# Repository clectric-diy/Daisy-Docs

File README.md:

# DaisyDocs
An augmented collection of the documentation provided by daisy.audio.

Documents in the [source folder](source) are those provided by daisy.audio under the MIT License.

clectric.diy community documents should be added to the [community folder](community).

All of the documentation in this repository is shared under the CC BY-SA license.

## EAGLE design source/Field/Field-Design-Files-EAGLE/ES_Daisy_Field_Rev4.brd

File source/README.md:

daisy.audio Documentation

All documentation in this source folder has been provided by daisy.audio under the MIT License.

Please see the [community folder](../community) for documentation created by the clectric.diy Community to augment what has been provided by daisy.audio.

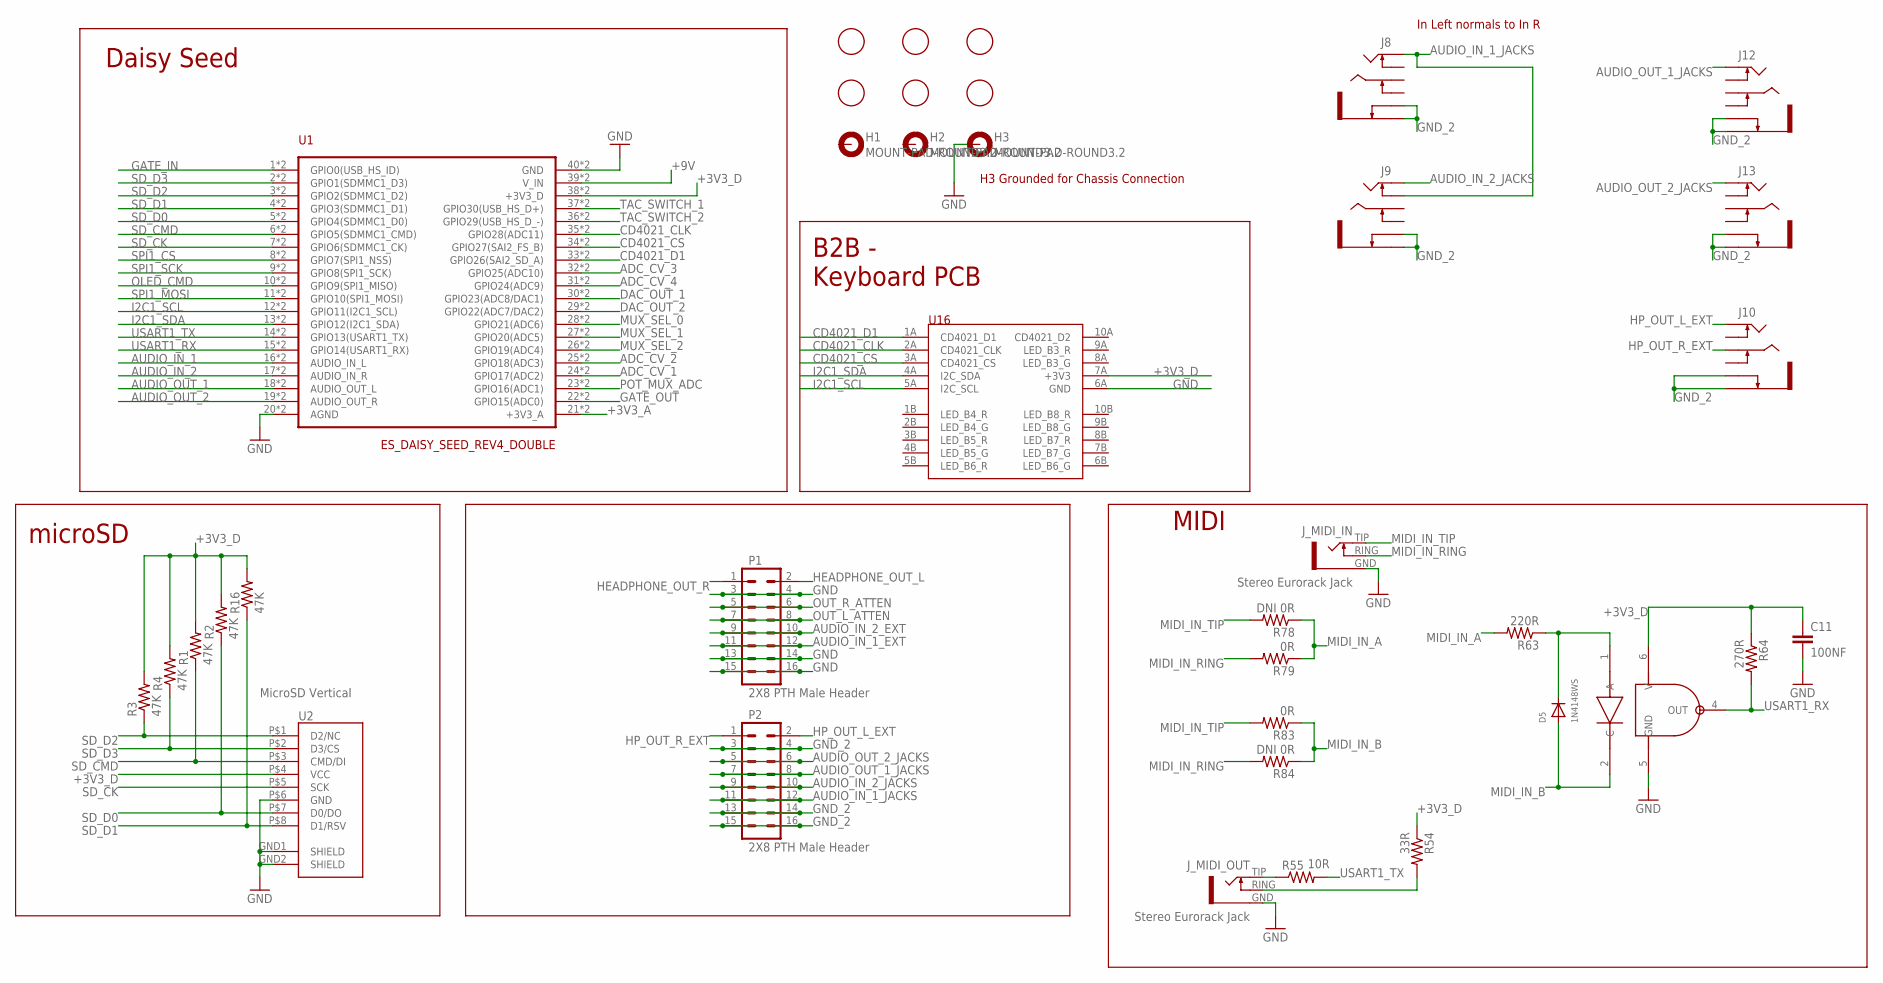
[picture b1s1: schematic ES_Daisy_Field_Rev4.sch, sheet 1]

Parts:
C11: 100NF; C0603
D5: 1N4148WS; SOD-323F
FD1, FD2, FD3, FD4, FD5, FD6: FIDUCIAL; FIDUCIAL_1MM
H1, H2, H3: MOUNT-PAD-ROUND3.2; 32-PAD
J8, J9, J10, J12, J13: PTH Switching Stereo Guitar Jack; WQP-PJ6110
J_MIDI_IN: Stereo Eurorack Jack; STEREO_JACK_3.5MM
J_MIDI_OUT: Stereo Eurorack Jack; STEREO_JACK_3.5MM
P1, P2: 2X8 PTH Male Header; 2X8_LOCK
R1, R2, R3, R4, R16: 47K; R0603
R54: 33R; R0603
R55: 10R; R0603
R63: 220R; R0603
R64: 270R; R0603
R78, R84: DNI 0R; R0603
R79, R83: 0R; R0603
U1: ES_DAISY_SEED_REV4_DOUBLE; ES_DAISY_SEED_DOUBLE
U2: MicroSD Vertical; VERT_MICROSD_CENTERED
U15: OPTO ISOLATOR; DIL06_GULLWING
U16: ES_KEYBOARD_SM_REV2_ALIGNED

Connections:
+3V3_A: U1.21 (+3V3_A), U1.B21 (+3V3_A); also elsewhere on the board
+3V3_D: C11.1, R1.2, R2.2, R3.2, R4.2, R16.2, R54.1, R64.1, U1.38 (+3V3_D), U1.B38 (+3V3_D), U2.P$4 (VCC), U15.6 (V), U16.7A (+3V3); also elsewhere on the board
+9V: U1.39 (V_IN), U1.B39 (V_IN); also elsewhere on the board
ADC_CV_1: U1.24 (GPIO17(ADC2)), U1.B24 (GPIO17(ADC2)); also elsewhere on the board
ADC_CV_2: U1.25 (GPIO18(ADC3)), U1.B25 (GPIO18(ADC3)); also elsewhere on the board
ADC_CV_3: U1.32 (GPIO25(ADC10)), U1.B32 (GPIO25(ADC10)); also elsewhere on the board
ADC_CV_4: U1.31 (GPIO24(ADC9)), U1.B31 (GPIO24(ADC9)); also elsewhere on the board
AUDIO_IN_1: U1.16 (AUDIO_IN_L), U1.B16 (AUDIO_IN_L); also elsewhere on the board
AUDIO_IN_1_EXT: P1.11, P1.12; also elsewhere on the board
AUDIO_IN_1_JACKS: J8.2 (TIP), J9.5 (TIP_SW), P2.11, P2.12
AUDIO_IN_2: U1.17 (AUDIO_IN_R), U1.B17 (AUDIO_IN_R); also elsewhere on the board
AUDIO_IN_2_EXT: P1.9, P1.10; also elsewhere on the board
AUDIO_IN_2_JACKS: J9.2 (TIP), P2.9, P2.10
AUDIO_OUT_1: U1.18 (AUDIO_OUT_L), U1.B18 (AUDIO_OUT_L); also elsewhere on the board
AUDIO_OUT_1_JACKS: J12.2 (TIP), P2.7, P2.8
AUDIO_OUT_2: U1.19 (AUDIO_OUT_R), U1.B19 (AUDIO_OUT_R); also elsewhere on the board
AUDIO_OUT_2_JACKS: J13.2 (TIP), P2.5, P2.6
CD4021_CLK: U1.35 (GPIO28(ADC11)), U1.B35 (GPIO28(ADC11)), U16.2A (CD4021_CLK)
CD4021_CS: U1.34 (GPIO27(SAI2_FS_B)), U1.B34 (GPIO27(SAI2_FS_B)), U16.3A (CD4021_CS)
CD4021_D1: U1.33 (GPIO26(SAI2_SD_A)), U1.B33 (GPIO26(SAI2_SD_A)), U16.1A (CD4021_D1)
DAC_OUT_1: U1.30 (GPIO23(ADC8/DAC1)), U1.B30 (GPIO23(ADC8/DAC1)); also elsewhere on the board
DAC_OUT_2: U1.29 (GPIO22(ADC7/DAC2)), U1.B29 (GPIO22(ADC7/DAC2)); also elsewhere on the board
GATE_IN: U1.1 (GPIO0(USB_HS_ID)), U1.B1 (GPIO0(USB_HS_ID)); also elsewhere on the board
GATE_OUT: U1.22 (GPIO15(ADC0)), U1.B22 (GPIO15(ADC0)); also elsewhere on the board
GND: C11.2, H3.B3,2, J_MIDI_IN.GND, J_MIDI_OUT.GND, P1.3, P1.4, P1.13, P1.14, P1.15, P1.16, U1.20 (AGND), U1.40 (GND), U1.B20 (AGND), U1.B40 (GND), U2.GND1 (SHIELD), U2.GND2 (SHIELD), U2.P$6 (GND), U15.5 (GND), U16.6A (GND); also elsewhere on the board
GND_2: J8.1 (SLEEVE), J8.4 (SLEEVE_SW), J9.1 (SLEEVE), J9.4 (SLEEVE_SW), J10.1 (SLEEVE), J10.4 (SLEEVE_SW), J12.1 (SLEEVE), J12.4 (SLEEVE_SW), J13.1 (SLEEVE), J13.4 (SLEEVE_SW), P2.3, P2.4, P2.13, P2.14, P2.15, P2.16
HEADPHONE_OUT_L: P1.2; also elsewhere on the board
HEADPHONE_OUT_R: P1.1; also elsewhere on the board
HP_OUT_L_EXT: J10.2 (TIP), P2.2
HP_OUT_R_EXT: J10.3 (RING), P2.1
I2C1_SCL: U1.12 (GPIO11(I2C1_SCL)), U1.B12 (GPIO11(I2C1_SCL)), U16.5A (I2C_SCL); also elsewhere on the board
I2C1_SDA: U1.13 (GPIO12(I2C1_SDA)), U1.B13 (GPIO12(I2C1_SDA)), U16.4A (I2C_SDA); also elsewhere on the board
MIDI_IN_A: R63.2, R78.1, R79.1
MIDI_IN_B: D5.A, R83.1, R84.1, U15.2 (C)
MIDI_IN_RING: J_MIDI_IN.RING (NORM), R79.2, R84.2
MIDI_IN_TIP: J_MIDI_IN.TIP, R78.2, R83.2
MUX_SEL_0: U1.28 (GPIO21(ADC6)), U1.B28 (GPIO21(ADC6)); also elsewhere on the board
MUX_SEL_1: U1.27 (GPIO20(ADC5)), U1.B27 (GPIO20(ADC5)); also elsewhere on the board
MUX_SEL_2: U1.26 (GPIO19(ADC4)), U1.B26 (GPIO19(ADC4)); also elsewhere on the board
unnamed: J_MIDI_OUT.TIP, R55.1
unnamed: J_MIDI_OUT.RING (NORM), R54.2
unnamed: D5.C, R63.1, U15.1 (A)
OLED_CMD: U1.10 (GPIO9(SPI1_MISO)), U1.B10 (GPIO9(SPI1_MISO)); also elsewhere on the board
OUT_L_ATTEN: P1.7, P1.8; also elsewhere on the board
OUT_R_ATTEN: P1.5, P1.6; also elsewhere on the board
POT_MUX_ADC: U1.23 (GPIO16(ADC1)), U1.B23 (GPIO16(ADC1)); also elsewhere on the board
SD_CK: U1.7 (GPIO6(SDMMC1_CK)), U1.B7 (GPIO6(SDMMC1_CK)), U2.P$5 (SCK)
SD_CMD: R1.1, U1.6 (GPIO5(SDMMC1_CMD)), U1.B6 (GPIO5(SDMMC1_CMD)), U2.P$3 (CMD/DI)
SD_D0: R2.1, U1.5 (GPIO4(SDMMC1_D0)), U1.B5 (GPIO4(SDMMC1_D0)), U2.P$7 (D0/DO)
SD_D1: R16.1, U1.4 (GPIO3(SDMMC1_D1)), U1.B4 (GPIO3(SDMMC1_D1)), U2.P$8 (D1/RSV)
SD_D2: R3.1, U1.3 (GPIO2(SDMMC1_D2)), U1.B3 (GPIO2(SDMMC1_D2)), U2.P$1 (D2/NC)
SD_D3: R4.1, U1.2 (GPIO1(SDMMC1_D3)), U1.B2 (GPIO1(SDMMC1_D3)), U2.P$2 (D3/CS)
SPI1_CS: U1.8 (GPIO7(SPI1_NSS)), U1.B8 (GPIO7(SPI1_NSS)); also elsewhere on the board
SPI1_MOSI: U1.11 (GPIO10(SPI1_MOSI)), U1.B11 (GPIO10(SPI1_MOSI)); also elsewhere on the board
SPI1_SCK: U1.9 (GPIO8(SPI1_SCK)), U1.B9 (GPIO8(SPI1_SCK)); also elsewhere on the board
TAC_SWITCH_1: U1.37 (GPIO30(USB_HS_D+)), U1.B37 (GPIO30(USB_HS_D+)); also elsewhere on the board
TAC_SWITCH_2: U1.36 (GPIO29(USB_HS_D_-)), U1.B36 (GPIO29(USB_HS_D_-)); also elsewhere on the board
USART1_RX: R64.2, U1.15 (GPIO14(USART1_RX)), U1.B15 (GPIO14(USART1_RX)), U15.4 (OUT)
USART1_TX: R55.2, U1.14 (GPIO13(USART1_TX)), U1.B14 (GPIO13(USART1_TX))

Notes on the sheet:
Daisy Seed
microSD
B2B - Keyboard PCB
MIDI
H3 Grounded for Chassis Connection
In Left normals to In R

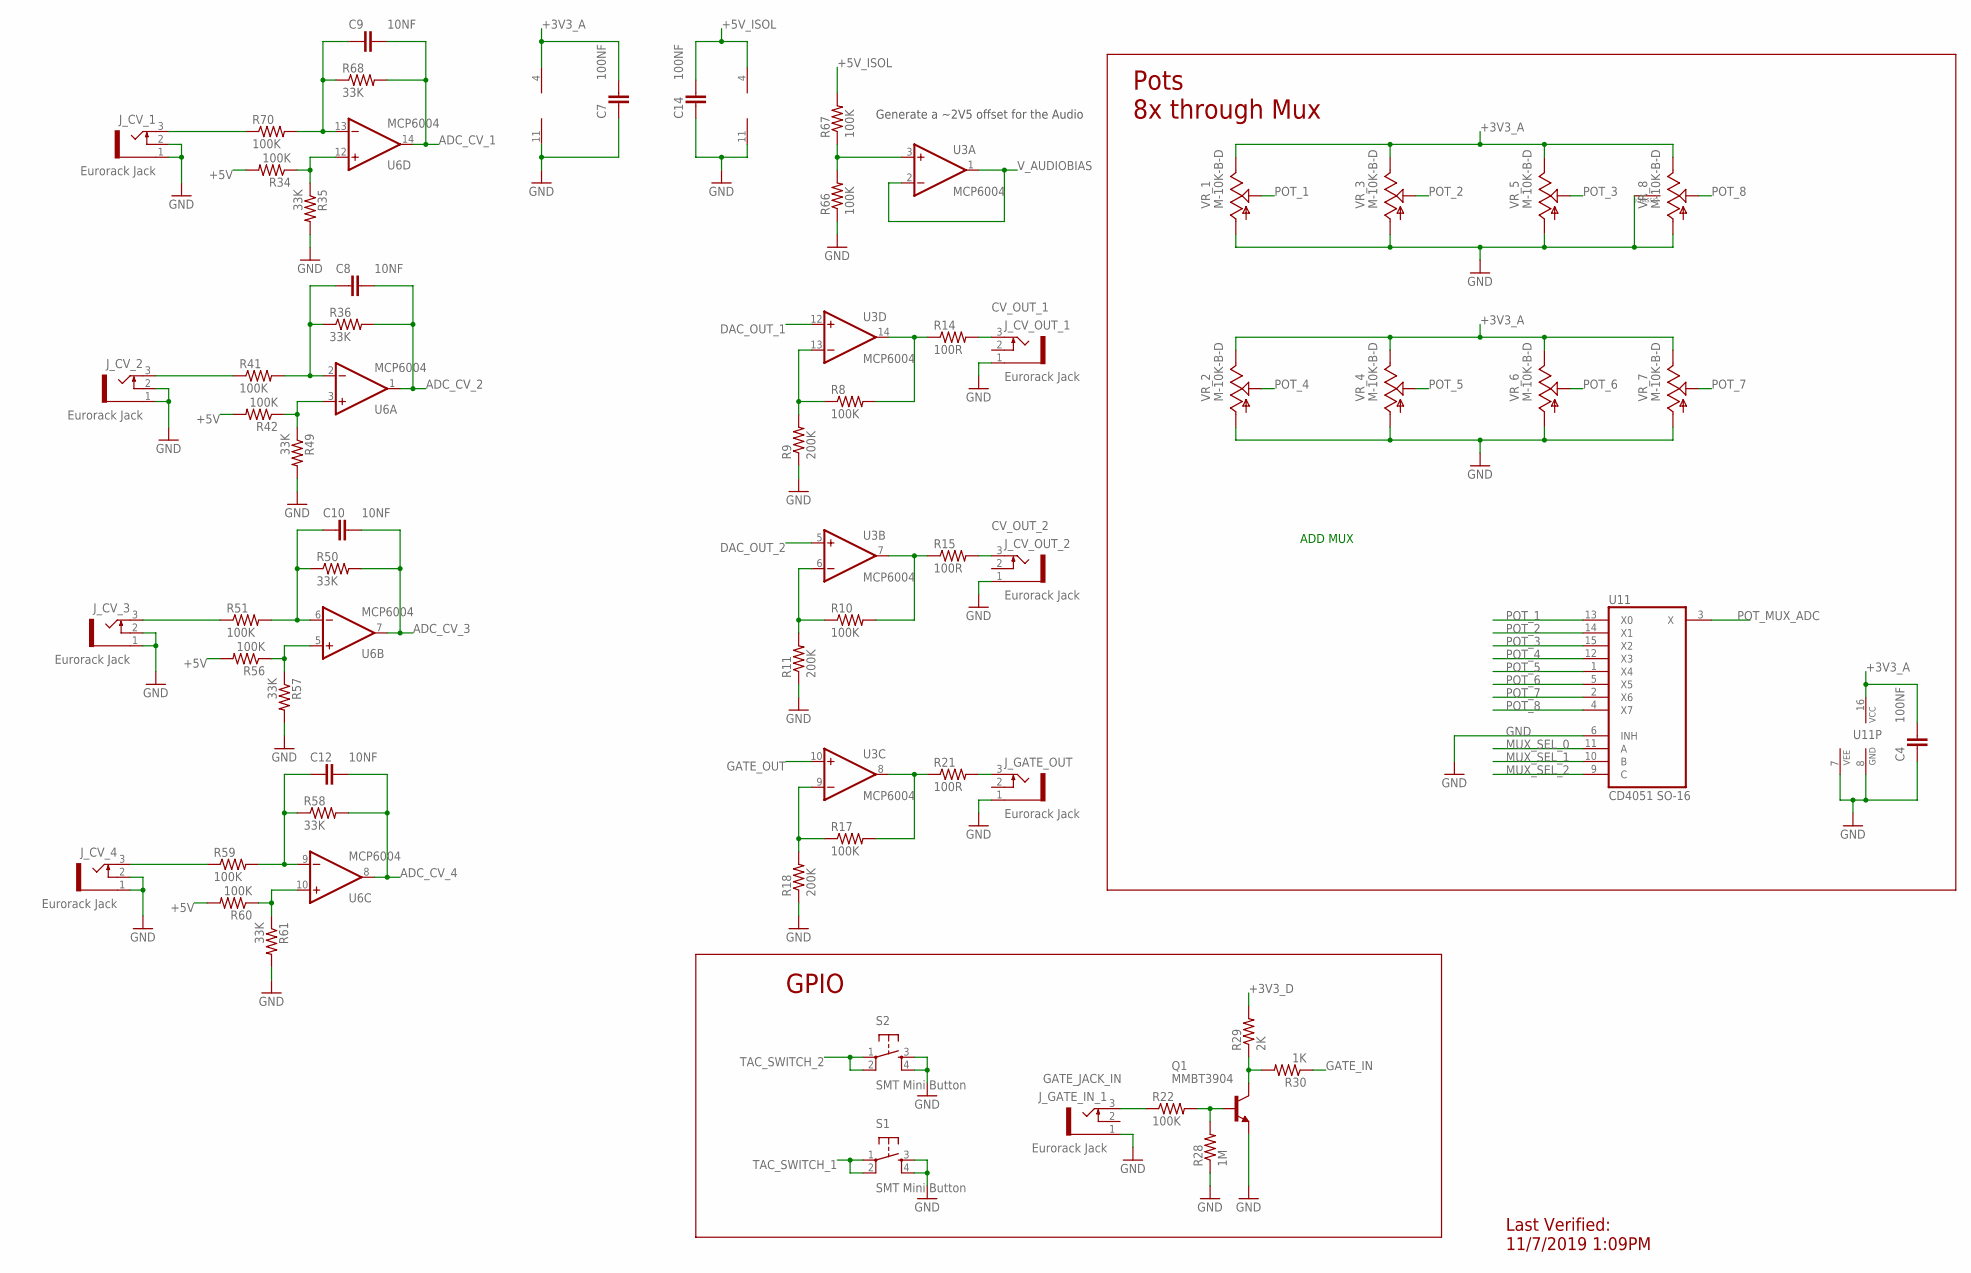
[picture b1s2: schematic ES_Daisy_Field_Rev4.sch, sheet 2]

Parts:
C4, C7, C14: 100NF; C0603
C8, C9, C10, C12: 10NF; C0603
J_CV_1, J_CV_2, J_CV_3, J_CV_4: Eurorack Jack; SMT_JACK
J_CV_OUT_1, J_CV_OUT_2: Eurorack Jack; SMT_JACK
J_GATE_IN_1: Eurorack Jack; SMT_JACK
J_GATE_OUT: Eurorack Jack; SMT_JACK
Q1: MMBT3904; SOT23-BEC
R8, R10, R17, R22, R34, R41, R42, R51, R56, R59, R60, R66, R67, R70: 100K; R0603
R9, R11, R18: 200K; R0603
R14, R15, R21: 100R; R0603
R28: 1M; R0603
R29: 2K; R0603
R30: 1K; R0603
R35, R36, R49, R50, R57, R58, R61, R68: 33K; R0603
S1, S2: SMT Mini Button; TL3301SPF160QJ
U3, U6: MCP6004; TSSOP-14
U11: CD4051 SO-16; SO-16
VR_1, VR_2, VR_3, VR_4, VR_5, VR_6, VR_7, VR_8: M-10K-B-D; 9MM_SNAP-IN_POT_SILK

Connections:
+3V3_A: C4.2, C7.2, U6.4 (V+), U11.16 (VCC), VR_1.3, VR_2.3, VR_3.3, VR_4.3, VR_5.3, VR_6.3, VR_7.3, VR_8.3 (E); also elsewhere on the board
+3V3_D: R29.2; also elsewhere on the board
+5V: R34.2, R42.2, R56.2, R60.2; also elsewhere on the board
+5V_ISOL: C14.2, R67.2, U3.4 (V+); also elsewhere on the board
ADC_CV_1: C9.2, R68.2, U6.14 (OUT); also elsewhere on the board
ADC_CV_2: C8.2, R36.2, U6.1 (OUT); also elsewhere on the board
ADC_CV_3: C10.2, R50.2, U6.7 (OUT); also elsewhere on the board
ADC_CV_4: C12.2, R58.2, U6.8 (OUT); also elsewhere on the board
CV_OUT_1: J_CV_OUT_1.3 (TIP), R14.2
CV_OUT_2: J_CV_OUT_2.3 (TIP), R15.2
CV_OUT_3: J_GATE_OUT.3 (TIP), R21.2
DAC_OUT_1: U3.12 (+IN); also elsewhere on the board
DAC_OUT_2: U3.5 (+IN); also elsewhere on the board
GATE_IN: R30.1; also elsewhere on the board
GATE_JACK_IN: J_GATE_IN_1.3 (TIP), R22.1
GATE_OUT: U3.10 (+IN); also elsewhere on the board
GND: C4.1, C7.1, C14.1, J_CV_1.1 (GND), J_CV_1.2 (NORM), J_CV_2.1 (GND), J_CV_2.2 (NORM), J_CV_3.1 (GND), J_CV_3.2 (NORM), J_CV_4.1 (GND), J_CV_4.2 (NORM), J_CV_OUT_1.1 (GND), J_CV_OUT_2.1 (GND), J_GATE_IN_1.1 (GND), J_GATE_OUT.1 (GND), Q1.E, R9.1, R11.1, R18.1, R28.1, R35.2, R49.2, R57.2, R61.2, R66.1, S1.3, S1.4, S2.3, S2.4, U3.11 (V-), U6.11 (V-), U11.6 (INH), U11.7 (VEE), U11.8 (GND), VR_1.1, VR_2.1, VR_3.1, VR_4.1, VR_5.1, VR_6.1, VR_7.1, VR_8.1 (A), VR_8.CHASSIS1 (CHASSIS), VR_8.CHASSIS2 (CHASSIS); also elsewhere on the board
MUX_SEL_0: U11.11 (A); also elsewhere on the board
MUX_SEL_1: U11.10 (B); also elsewhere on the board
MUX_SEL_2: U11.9 (C); also elsewhere on the board
unnamed: R10.2, R15.1, U3.7 (OUT)
unnamed: R8.2, R14.1, U3.14 (OUT)
unnamed: R8.1, R9.2, U3.13 (-IN)
unnamed: R34.1, R35.1, U6.12 (+IN)
unnamed: R10.1, R11.2, U3.6 (-IN)
unnamed: C8.1, R36.1, R41.2, U6.2 (-IN)
unnamed: Q1.C, R29.1, R30.2
unnamed: J_CV_2.3 (TIP), R41.1
unnamed: R42.1, R49.1, U6.3 (+IN)
unnamed: R17.2, R21.1, U3.8 (OUT)
unnamed: R17.1, R18.2, U3.9 (-IN)
unnamed: C10.1, R50.1, R51.2, U6.6 (-IN)
unnamed: J_CV_3.3 (TIP), R51.1
unnamed: R56.1, R57.1, U6.5 (+IN)
unnamed: C12.1, R58.1, R59.2, U6.9 (-IN)
unnamed: J_CV_4.3 (TIP), R59.1
unnamed: R60.1, R61.1, U6.10 (+IN)
unnamed: Q1.B, R22.2, R28.2
unnamed: R66.2, R67.1, U3.3 (+IN)
unnamed: C9.1, R68.1, R70.2, U6.13 (-IN)
unnamed: J_CV_1.3 (TIP), R70.1
POT_1: U11.13 (X0), VR_1.2
POT_2: U11.14 (X1), VR_3.2
POT_3: U11.15 (X2), VR_5.2
POT_4: U11.12 (X3), VR_2.2
POT_5: U11.1 (X4), VR_4.2
POT_6: U11.5 (X5), VR_6.2
POT_7: U11.2 (X6), VR_7.2
POT_8: U11.4 (X7), VR_8.2 (S)
POT_MUX_ADC: U11.3 (X); also elsewhere on the board
TAC_SWITCH_1: S1.1, S1.2; also elsewhere on the board
TAC_SWITCH_2: S2.1, S2.2; also elsewhere on the board
V_AUDIOBIAS: U3.1 (OUT), U3.2 (-IN); also elsewhere on the board

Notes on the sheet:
Pots 8x through Mux
GPIO
ADD MUX
Last Verified: 11/7/2019 1:09PM
Generate a ~2V5 offset for the Audio

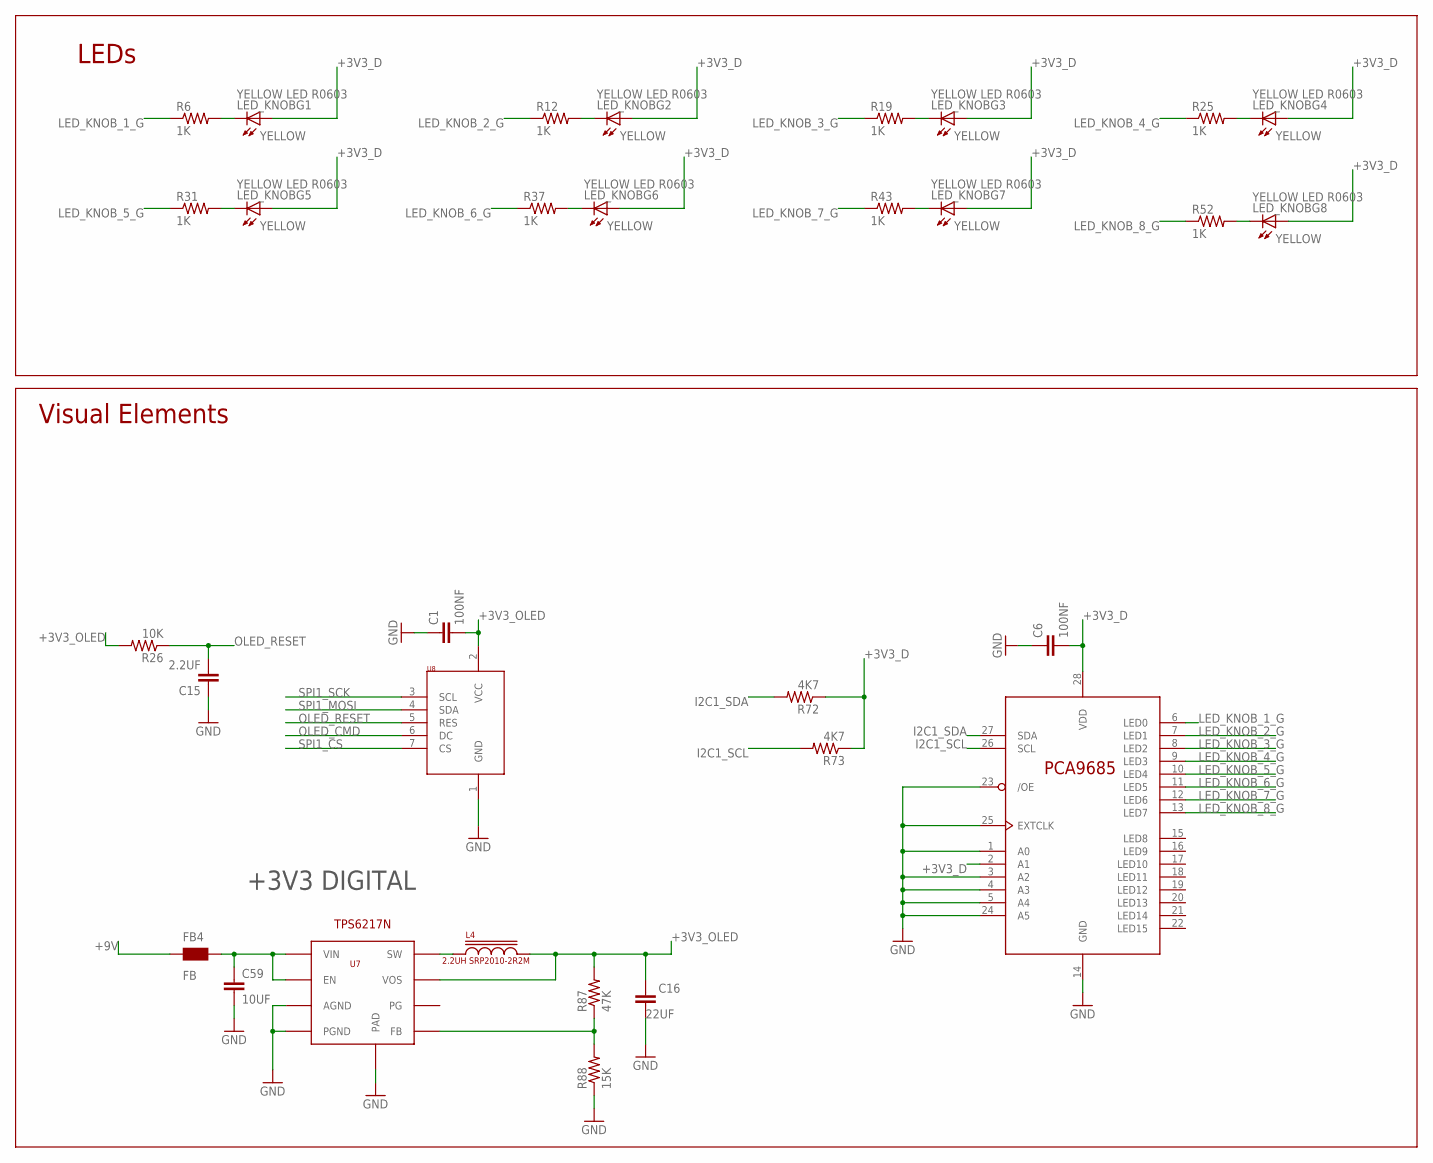
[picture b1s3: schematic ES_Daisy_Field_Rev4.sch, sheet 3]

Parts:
C1, C6: 100NF; C0603
C15: 2.2UF; C0603
C16: 22UF; C1206
C59: 10UF; C0805
FB4: FB; WUERTH-ELEKTRONIK_0603
L4: 2.2UH SRP2010-2R2M; BOURNS_SRP2010
LED_KNOBG1, LED_KNOBG2, LED_KNOBG3, LED_KNOBG4, LED_KNOBG5, LED_KNOBG6, LED_KNOBG7, LED_KNOBG8: YELLOW LED R0603; DIODE_0603
R6, R12, R19, R25, R31, R37, R43, R52: 1K; R0603
R26: 10K; R0603
R72, R73: 4K7; R0603
R87: 47K; R0603
R88: 15K; R0603
U5: PCA9685 TSSOP-28; TSSOP-28
U7: TPS62170 WSON-8; WSON-8
U8: OLED_DISPLAY; ER-OLEDM015-2

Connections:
+3V3_D: C6.2, LED_KNOBG1.ANODE (A), LED_KNOBG2.ANODE (A), LED_KNOBG3.ANODE (A), LED_KNOBG4.ANODE (A), LED_KNOBG5.ANODE (A), LED_KNOBG6.ANODE (A), LED_KNOBG7.ANODE (A), LED_KNOBG8.ANODE (A), R72.1, R73.1, U5.2 (A1), U5.28 (VDD); also elsewhere on the board
+3V3_OLED: C1.2, C16.1, L4.P$2, R26.2, R87.2, U7.6 (VOS), U8.2 (VCC)
+9V: FB4.1; also elsewhere on the board
GND: C1.1, C6.1, C15.1, C16.2, C59.2, R88.1, U5.1 (A0), U5.3 (A2), U5.4 (A3), U5.5 (A4), U5.14 (GND), U5.23 (/OE), U5.24 (A5), U5.25 (EXTCLK), U7.1 (PGND), U7.4 (AGND), U7.P$1 (PAD), U7.P$9 (PAD), U8.1 (GND); also elsewhere on the board
I2C1_SCL: R73.2, U5.26 (SCL); also elsewhere on the board
I2C1_SDA: R72.2, U5.27 (SDA); also elsewhere on the board
LED_KNOB_1_G: R6.1, U5.6 (LED0)
LED_KNOB_2_G: R12.1, U5.7 (LED1)
LED_KNOB_3_G: R19.1, U5.8 (LED2)
LED_KNOB_4_G: R25.1, U5.9 (LED3)
LED_KNOB_5_G: R31.1, U5.10 (LED4)
LED_KNOB_6_G: R37.1, U5.11 (LED5)
LED_KNOB_7_G: R43.1, U5.12 (LED6)
LED_KNOB_8_G: R52.1, U5.13 (LED7)
unnamed: LED_KNOBG1.CATHODE (C), R6.2
unnamed: LED_KNOBG2.CATHODE (C), R12.2
unnamed: LED_KNOBG3.CATHODE (C), R19.2
unnamed: LED_KNOBG4.CATHODE (C), R25.2
unnamed: LED_KNOBG5.CATHODE (C), R31.2
unnamed: LED_KNOBG6.CATHODE (C), R37.2
unnamed: LED_KNOBG7.CATHODE (C), R43.2
unnamed: LED_KNOBG8.CATHODE (C), R52.2
unnamed: C59.1, FB4.2, U7.2 (VIN), U7.3 (EN)
unnamed: R87.1, R88.2, U7.5 (FB)
unnamed: L4.P$1, U7.7 (SW)
OLED_CMD: U8.6 (DC); also elsewhere on the board
OLED_RESET: C15.2, R26.1, U8.5 (RES)
SPI1_CS: U8.7 (CS); also elsewhere on the board
SPI1_MOSI: U8.4 (SDA); also elsewhere on the board
SPI1_SCK: U8.3 (SCL); also elsewhere on the board

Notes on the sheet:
Visual Elements
LEDs
+3V3 DIGITAL

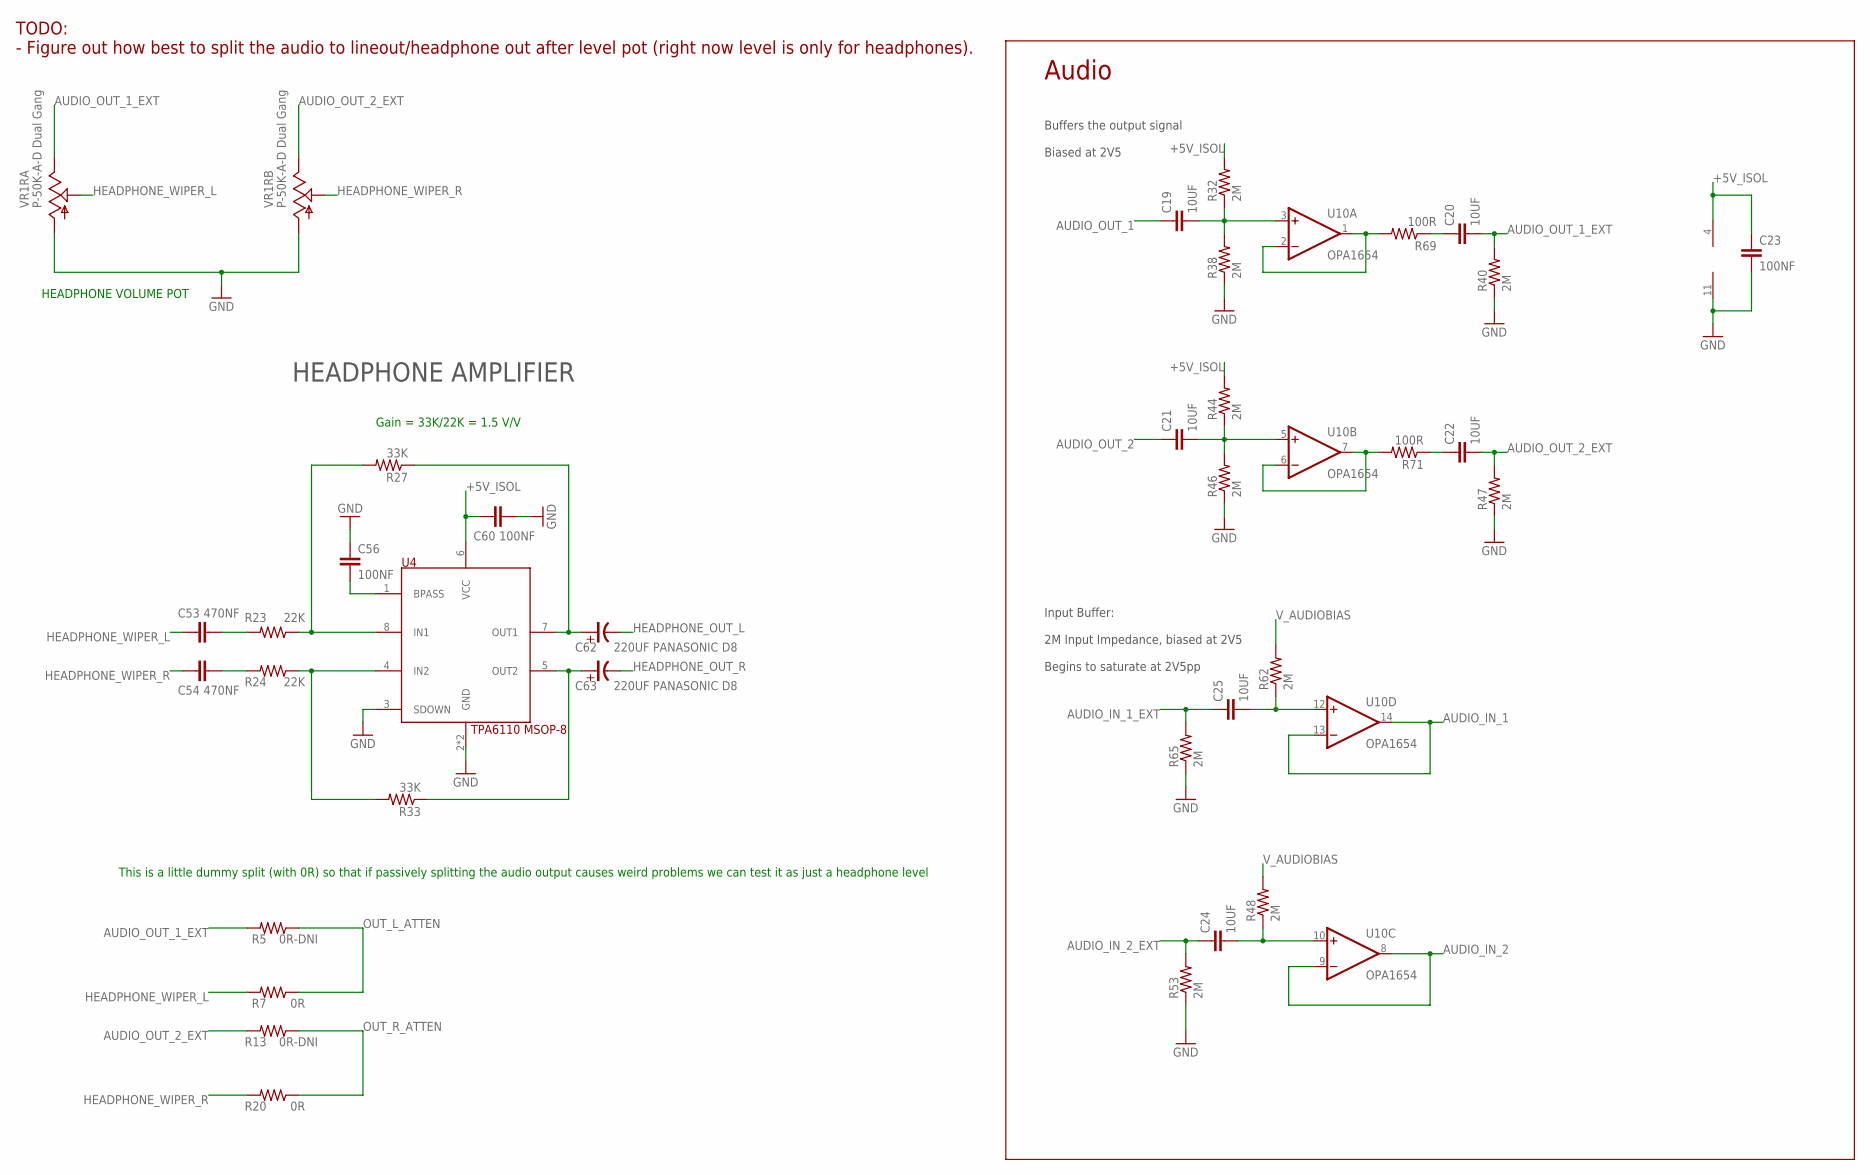
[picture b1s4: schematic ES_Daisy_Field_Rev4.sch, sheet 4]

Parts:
C19, C20, C21, C22, C24, C25: 10UF; C0805
C23, C56, C60: 100NF; C0603
C53, C54: 470NF; C0603
C62, C63: 220UF PANASONIC D8; PANASONIC_D
R5, R13: 0R-DNI; R0603
R7, R20: 0R; R0603
R23, R24: 22K; R0603
R27, R33: 33K; R0603
R32, R38, R40, R44, R46, R47, R48, R53, R62, R65: 2M; R0603
R69, R71: 100R; R0603
U4: TPA6110 MSOP-8; MSOP_8_PWRPAD
U10: OPA1654; TSSOP-14
VR1: P-50K-A-D Dual Gang; BOURNS_PTV112_SILK

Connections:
+5V_ISOL: C23.1, C60.2, R32.2, R44.2, U4.6 (VCC), U10.4 (V+); also elsewhere on the board
AUDIO_IN_1: U10.13 (-IN), U10.14 (OUT); also elsewhere on the board
AUDIO_IN_1_EXT: C25.1, R65.2; also elsewhere on the board
AUDIO_IN_2: U10.8 (OUT), U10.9 (-IN); also elsewhere on the board
AUDIO_IN_2_EXT: C24.1, R53.2; also elsewhere on the board
AUDIO_OUT_1: C19.1; also elsewhere on the board
AUDIO_OUT_1_EXT: C20.2, R5.2, R40.2, VR1.3P (3)
AUDIO_OUT_2: C21.1; also elsewhere on the board
AUDIO_OUT_2_EXT: C22.2, R13.2, R47.2, VR1.3
GND: C23.2, C56.1, C60.1, R38.1, R40.1, R46.1, R47.1, R53.1, R65.1, U4.2 (GND), U4.3 (SDOWN), U4.9 (GND), U10.11 (V-), VR1.1, VR1.1P (1); also elsewhere on the board
HEADPHONE_OUT_L: C62.- (NEG); also elsewhere on the board
HEADPHONE_OUT_R: C63.- (NEG); also elsewhere on the board
HEADPHONE_WIPER_L: C53.1, R7.2, VR1.2P (2)
HEADPHONE_WIPER_R: C54.1, R20.2, VR1.2
unnamed: C54.2, R24.2
unnamed: C19.2, R32.1, R38.2, U10.3 (+IN)
unnamed: R23.1, R27.2, U4.8 (IN1)
unnamed: R24.1, R33.2, U4.4 (IN2)
unnamed: R69.2, U10.1 (OUT), U10.2 (-IN)
unnamed: C21.2, R44.1, R46.2, U10.5 (+IN)
unnamed: R71.2, U10.6 (-IN), U10.7 (OUT)
unnamed: C53.2, R23.2
unnamed: C24.2, R48.1, U10.10 (+IN)
unnamed: C25.2, R62.1, U10.12 (+IN)
unnamed: C56.2, U4.1 (BPASS)
unnamed: C62.+ (POS), R27.1, U4.7 (OUT1)
unnamed: C63.+ (POS), R33.1, U4.5 (OUT2)
unnamed: C20.1, R69.1
unnamed: C22.1, R71.1
OUT_L_ATTEN: R5.1, R7.1; also elsewhere on the board
OUT_R_ATTEN: R13.1, R20.1; also elsewhere on the board
V_AUDIOBIAS: R48.2, R62.2; also elsewhere on the board

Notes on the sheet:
HEADPHONE VOLUME POT
HEADPHONE AMPLIFIER
Gain = 33K/22K = 1.5 V/V
TODO: - Figure out how best to split the audio to lineout/headphone out after level pot (right now level is only for headphones).
This is a little dummy split (with 0R) so that if passively splitting the audio output causes weird problems we can test it as just a headphone level
Buffers the output signal Biased at 2V5
Audio
Input Buffer: 2M Input Impedance, biased at 2V5 Begins to saturate at 2V5pp

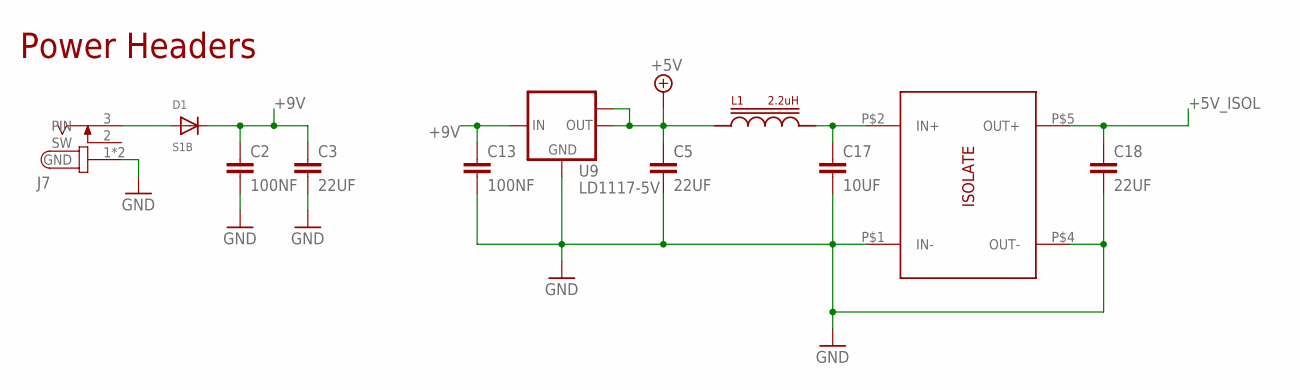
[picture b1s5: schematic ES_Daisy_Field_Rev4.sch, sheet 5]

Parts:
C2, C13: 100NF; C0603
C3, C18: 22UF; C1206
C5: 22UF; C0805
C17: 10UF; C0805
D1: S1B; SMADIODE
J7: SMT GUITAR DC JACK; WQP-DC0500
L1: 2.2uH; BOURNS_SRP2010
U9: LD1117-5V; SOT223
U$4: POWER_ISOLATE; XP_POWER_ISEXXXXA

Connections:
+5V: C5.1, L1.P$1, U9.2 (OUT), U9.TAB (OUT1); also elsewhere on the board
+5V_ISOL: C18.1, U$4.P$5 (OUT+); also elsewhere on the board
+9V: C2.1, C3.1, C13.1, D1.C, U9.3 (IN); also elsewhere on the board
GND: C2.2, C3.2, C5.2, C13.2, C17.2, C18.2, J7.1 (GND), J7.4 (GND), U9.1 (GND), U$4.P$1 (IN-), U$4.P$4 (OUT-); also elsewhere on the board
unnamed: D1.A, J7.3 (PIN)
unnamed: C17.1, L1.P$2, U$4.P$2 (IN+)

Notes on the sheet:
Power Headers

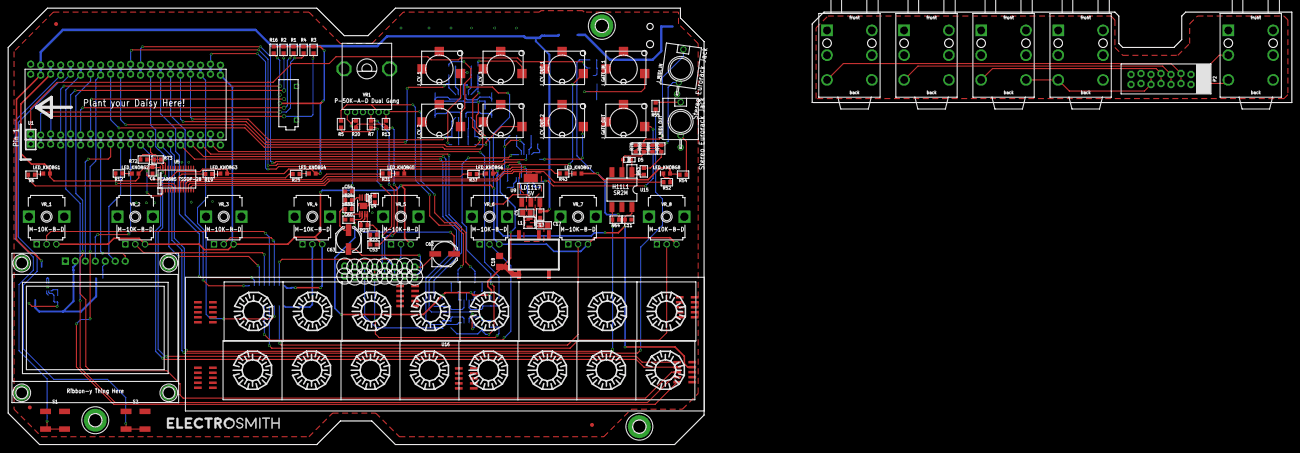
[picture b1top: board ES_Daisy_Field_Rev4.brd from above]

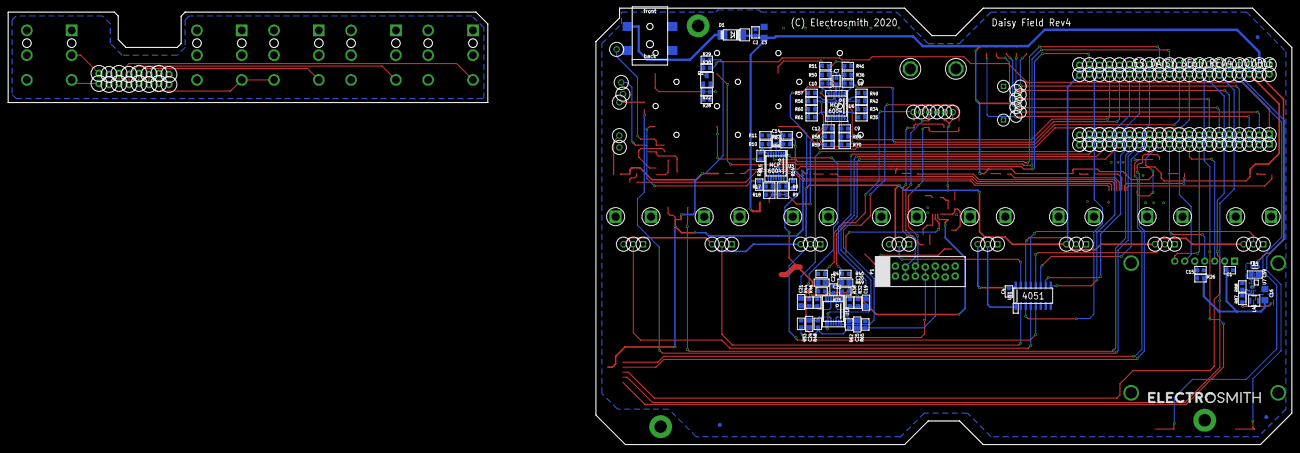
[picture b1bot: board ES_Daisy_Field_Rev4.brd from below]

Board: 2 copper layers, 326.5 x 111.0 mm, 179 parts (81 on the bottom side), 137 nets.

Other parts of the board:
U$1, U$2: ENCLOSURE_1590DD
U$3, U$7: ES_TEXT_3X30MM

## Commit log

2025-08-22 Create LICENSE
2025-08-22 Adding Docs from daisy.audio
2025-08-22 Adding explination of source and community directories.
2025-08-22 bump for pages
2025-08-22 Addint Architect Theme
2025-08-23 Add links to pinouts and BOMs
2025-08-23 links to directories
2025-08-23 highlighting the directory links
2025-08-23 is it folder or a dir?
    ... it's confusing these days.
2025-08-23 updating links
    trying to make the links work in both the GitHub and Pages views.
2025-08-23 don't get lost
2025-08-23 colemak typo
2025-08-23 updating links
    trying to keep the links flowing in docs and working both within GitHub and on Pages.
2025-08-23 Updated to match repo's name change
2025-08-24 Standard FUNDING & gitignore
2025-08-25 Removing Broken Analytics
2025-09-01 Adding Rotated schema from DaisyExamples Osc
2025-09-01 Moving files to subfolder daisy.audio to allow for a DaisyExamples, and other, subfolders.
2025-09-01 Added links to source and community notes for DaisyExamples.
2025-09-01 Clarifying the Header
2026-03-28 a "snapshot" of the EAGLE Files Provided by Electrosmith
2026-03-28 a "snapshot" of the KiCad Files Provided by Electrosmith
